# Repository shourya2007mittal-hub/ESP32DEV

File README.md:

# ESP32DEV

I made a custom Devboard based on ESP32-S3-WROOM-1 . It has voltage regulator , LED indicators , Boot Pin and the best part is that all the Pins available on the WROOM-1 is accessible via connector including BOOT, EN, DATA Lines.

## Features
- Base on  ESP32-S3-WROOM-1
- Has 3.3 V voltage regulator 
- All the possible WROOM-1 pins are accesible via pin connector

---

 | Top Designator | Comment | Footprint | Qty | Total Price (USD) | Product Link |
|:--------------|:--------|:----------|---:|------------------:|:-------------|
| C2 | 47uF | 0201 | 2 | $1.3330 | https://jlcpcb.com/partdetail/3127-KM476M450K25RR0VH2FP0/C2746 |
| C3 | 10uF | 0201 | 20 | $0.5860 | https://jlcpcb.com/partdetail/2043-CL10A106MQ8NNNC/C1691 |
| C4 | 100nF | 0201 | 20 | $0.1460 | https://jlcpcb.com/partdetail/MurataElectronics-GRM033R61A104KE15D/C76934 |
| C5, C6 | 22uF | 0201 | 8 | $2.5128 | https://jlcpcb.com/partdetail/2211-1206X226K100NT/C1859 |
| C5(1UF)1, C6(100NF)1 | C5(1UF)1, C6(100NF)1 | 0805 | 20 | $0.6440 | https://jlcpcb.com/partdetail/YAGEO-CC0805KRX7R9BB104/C49678 |
| D1, D2, D3 | LED | 0201 | 10 | $0.6810 | https://jlcpcb.com/partdetail/XINGLIGHT-XL0201SURC/C3646923 |
| D4 | 1N4001 | D_DO-41_SOD81_P2.54mm_Vertical_AnodeUp | 4 | $0.0776 | https://jlcpcb.com/partdetail/49200031-1N4001/C47018536 |
| L1 | 4.7uH | 0603 | 20 | $0.4140 | https://jlcpcb.com/partdetail/Sunlord-SDFL1608Q4R7KTF/C1034 |
| L2 | 2.2uH | 0603 | 20 | $0.5040 | https://jlcpcb.com/partdetail/270373-CMI160808U2R2KT/C284875 |
| Q1 | AO3401A | SOT-23 | 6 | $0.5946 | https://jlcpcb.com/partdetail/Alpha_OmegaSemicon-AO3401A/C15127 |
| R1, R2 | 33Ω | 0603 | 20 | $0.1580 | https://jlcpcb.com/partdetail/23867-0603WAF330JT5E/C23140 |
| R3, R4 | 50kΩ | 0603 | 20 | $0.6500 | https://jlcpcb.com/partdetail/YAGEO-RT0603BRD0750KL/C861451 |
| R6, R7, R8 | 1kΩ | 0201 | 20 | $0.0500 | https://jlcpcb.com/partdetail/259895-0201WMF1001TEE/C270365 |
| R1(10K)1, R2(100R)1 | R | 0805 | 6 | $0.5364 | https://jlcpcb.com/partdetail/FuzetecTech-FSMD050_0805R/C181350 |
| SW1, SW2 | Push Button | SW_SPST_PTS810 | 4 | $2.3948 | https://jlcpcb.com/partdetail/41719-DSHP02TSGET/C40735 |
| U5 | ESP32-S3-WROOM-1 | ESP32-S3-WROOM-1 | 2 | $10.8594 | https://jlcpcb.com/partdetail/3198300-ESP32_S3_WROOM_1N16R8/C2913202 |
| U2 | AP63203WU | TSOT-23-6 | 5 | $0.6019 | https://jlcpcb.com/partdetail/DiodesIncorporated-AP63203WU7/C780769 |
| PCB | PCB Fabrication | — | 1 | $4.00 | https://jlcpcb.com |
| SETUP | Assembly Setup Fee | — | 1 | $25.00 | https://jlcpcb.com |
| LOAD | Component Loading Fee | — | 1 | $14.00 | https://jlcpcb.com |
| SHIPPING | Shipping | — | 1 | $16.78 | https://jlcpcb.com |
| **TOTAL** | | | | **$82.5235** | https://jlcpcb.com |

### 💵 Cost Summary

| Item | Cost (USD) |
|------|-----------:|
| Components | $22.7435 |
| PCB Fabrication | $4.00 |
| Assembly Setup | $25.00 |
| Component Loading | $14.00 |
| Shipping | $16.78 |
| **Grand Total** | **$82.5235** |

### Schematic

###  PCB Design

### 3D Design

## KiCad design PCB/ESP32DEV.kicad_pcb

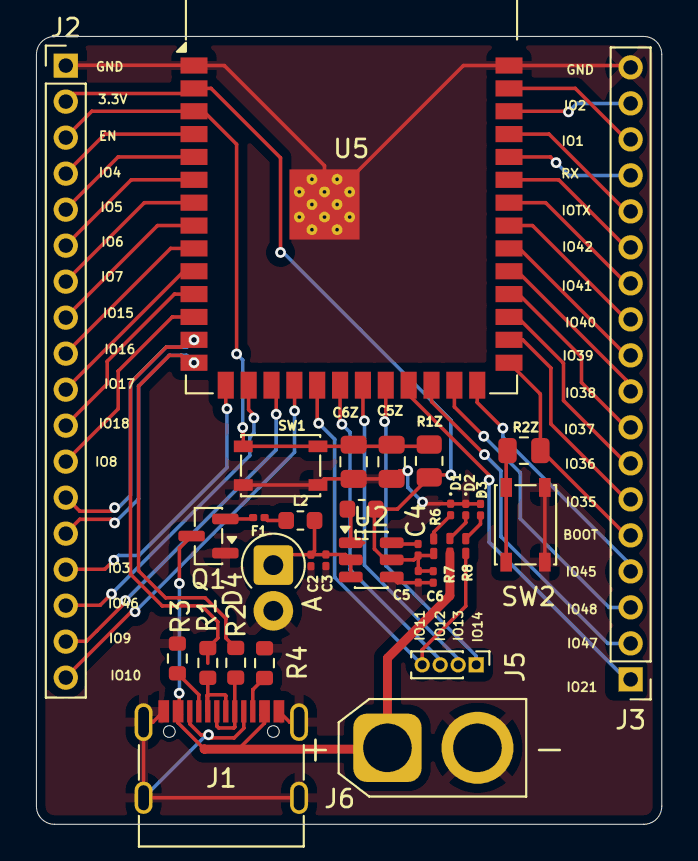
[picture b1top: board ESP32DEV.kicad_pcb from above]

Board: 2 copper layers, 34.7 x 43.8 mm, 33 parts (0 on the bottom side), 53 nets.

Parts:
C2: 47uf; C_0201_0603Metric
C3: 10uf; C_0201_0603Metric
C4: 100nf; C_0201_0603Metric
C5, C6: 22uf; C_0201_0603Metric
C5Z, C6Z: C; C_0805_2012Metric
D1, D2, D3: LED; LED_0201_0603Metric
D4: 1N4001; D_DO-41_SOD81_P2.54mm_Vertical_AnodeUp
F1: Polyfuse; C_0201_0603Metric
J1: USB_C_Receptacle_USB2.0_16P; USB_C_Receptacle_G-Switch_GT-USB-7010ASV
J2, J3: Conn_01x18_Pin; PinHeader_1x18_P2.00mm_Vertical
J5: Conn_01x04_Pin; PinHeader_1x04_P1.00mm_Vertical
J6: Conn_01x02_Pin; AMASS_XT30U-F_1x02_P5.0mm_Vertical
L1: 4.7uh; L_0603_1608Metric
L2: 2.2uh; L_0603_1608Metric
Q1: AO3401A; SOT-23
R1, R2: 33 R; R_0603_1608Metric
R1Z, R2Z: R; R_0805_2012Metric
R3, R4: 50K; R_0603_1608Metric
R6, R7, R8: 1K; R_0201_0603Metric_Pad0.64x0.40mm_HandSolder
SW1, SW2: SW_Push; SW_SPST_PTS810
U2: AP63203WU; TSOT-23-6
U5: ESP32-S3-WROOM-1

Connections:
+3.3V: C4.1, C5.1, C6.1, J2.2, L1.1, R1Z.1, R6.1, U2.5 (SW), U5.2 (3V3)
+5V: J1.A4 (VBUS), J1.A9 (VBUS), J1.B4 (VBUS), J1.B9 (VBUS), J6.1, Q1.3 (D), R7.2
BOOT: J3.5, R2Z.1, U5.27 (IO0)
EN: C5Z.1, C6Z.1, J2.3, R1Z.2, SW1.1, U5.3 (EN)
GND: C2.2, C3.2, C5.2, C5Z.2, C6.2, C6Z.2, D1.1 (K), D2.1 (K), D3.1 (K), D4.2 (A), J1.A1 (GND), J1.A8 (SBU1), J1.A12 (GND), J1.B1 (GND), J1.B8 (SBU2), J1.B12 (GND), J1.S1 (SHIELD), J2.1, J3.18, J6.2, Q1.1 (G), R3.2, R4.2, SW1.2, SW2.2, U2.4 (GND), U5.1 (GND), U5.40 (GND), U5.41 (GND)
I01: J3.16, U5.39 (IO1)
I02: J3.17, U5.38 (IO2)
I03: J2.15, U5.15 (IO3)
I04: J2.4, U5.4 (IO4)
I05: J2.5, U5.5 (IO5)
I06: J2.6, U5.6 (IO6)
I07: J2.7, U5.7 (IO7)
I08: J2.12, U5.12 (IO8)
I09: J2.17, U5.17 (IO9)
I010: J2.18, U5.18 (IO10)
I011: J5.4, R8.2, U5.19 (IO11)
I012: J5.3, U5.20 (IO12)
I013: J5.2, U5.21 (IO13)
I014: J5.1, U5.22 (IO14)
I015: J2.8, U5.8 (IO15)
I016: J2.9, U5.9 (IO16)
I017: J2.10, U5.10 (IO17)
I018: J2.11, U5.11 (IO18)
I021: J3.1, U5.23 (IO21)
I035: J3.6, U5.28 (IO35)
I036: J3.7, U5.29 (IO36)
I037: J3.8, U5.30 (IO37)
I038: J3.9, U5.31 (IO38)
I039: J3.10, U5.32 (IO39)
I040: J3.11, U5.33 (IO40)
I041: J3.12, U5.34 (IO41)
I042: J3.13, U5.35 (IO42)
I045: J3.4, U5.26 (IO45)
I046: J2.16, U5.16 (IO46)
I047: J3.2, U5.24 (IO47)
I048: J3.3, U5.25 (IO48)
unnamed: D1.2 (A), R6.2
unnamed: D2.2 (A), R7.1
unnamed: D3.2 (A), R8.1
unnamed: C2.1, C3.1, D4.1 (K), L2.2, U2.2 (EN), U2.3 (IN)
unnamed: F1.2, L2.1
unnamed: J1.A5 (CC1), R3.1
unnamed: J1.B5 (CC2), R4.1
unnamed: J1.A6 (D+), J1.B6 (D+), R2.1
unnamed: J1.A7 (D-), J1.B7 (D-), R1.1
unnamed: F1.1, Q1.2 (S)
unnamed: R2Z.2, SW2.1
unnamed: C4.2, U2.6 (BST)
unnamed: L1.2, U2.1 (FB)
RX: J3.15, U5.36 (RXD0)
TX: J3.14, U5.37 (TXD0)
_D+: J2.14, R2.2, U5.14 (USB_D+)
_D-: J2.13, R1.2, U5.13 (USB_D-)

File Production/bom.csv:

Designator,Footprint,Quantity,Value,LCSC Part #
C2,0201,1,47uf,
C3,0201,1,10uf,
C4,0201,1,100nf,
"C5, C6",0201,2,22uf,
"C5(1UF)1, C6(100NF)1",0805,2,C,
"D1, D2, D3",0201,3,LED,
D4,D_DO-41_SOD81_P2.54mm_Vertical_AnodeUp,1,1N4001,
F1,0201,1,Polyfuse,
J1,USB_C_Receptacle_G-Switch_GT-USB-7010ASV,1,USB_C_Receptacle_USB2.0_16P,
"J2, J3",PinHeader_1x18_P2.00mm_Vertical,2,Conn_01x18_Pin,
J5,PinHeader_1x04_P1.00mm_Vertical,1,Conn_01x04_Pin,
J6,AMASS_XT30U-F_1x02_P5.0mm_Vertical,1,Conn_01x02_Pin,
L1,0603,1,4.7uh,
L2,0603,1,2.2uh,
Q1,SOT-23,1,AO3401A,
"R1, R2",0603,2,33 R,
"R1(10K)1, R2(100R)1",0805,2,R,
"R3, R4",0603,2,50K,
"R6, R7, R8",0201,3,1K,
"SW1, SW2",SW_SPST_PTS810,2,SW_Push,
U2,TSOT-23-6,1,AP63203WU,
U5,ESP32-S3-WROOM-1,1,ESP32-S3-WROOM-1,
